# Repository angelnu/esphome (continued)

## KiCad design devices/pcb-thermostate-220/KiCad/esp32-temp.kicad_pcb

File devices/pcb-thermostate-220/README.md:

# Thermostate for 220v
This PCB allows controlling two relays based on 1 wire Dallas temperature sensors. The board has two 1-wire buses - one for the in-board sensor and one for the external sensor(s).
- 

- [Aisler PCB project](https://aisler.net/p/ORVQXQHK)
- [KiCad schematics](KiCad/esp32-temp.sch)
  - 
- [KiCad PCB](KiCad/esp32-temp.kicad_pcb)
  - 
  - 
  - 

- Parts:
  - 1x [ESP32-WROOM-32](https://www.espressif.com/sites/default/files/documentation/esp32-wroom-32_datasheet_en.pdf)
  - nx [Temperature Sensors - DS18B20](http://datasheets.maximintegrated.com/en/ds/DS18B20.pdf)
    - the sensor in the PCB is in format TO-92. I bought mine in ebay.
    - the external sensors are attached to the connector top lef. You can get them waterprof at many places including [Amazon](https://www.amazon.de/AZDelivery-digitaler-Temperatursensor-Temperaturf%C3%BChler-wasserdicht/dp/B075FV3PQR/ref=sr_1_8?dchild=1&keywords=DS18B20&qid=1598127886&sr=8-8)
  - 2x [5v 10A Relay](http://www.sanyourelay.ca/public/products/pdf/SRD.pdf)
  - 1x [220v-5V ACDC transformer](http://www.hlktech.net/product_detail.php?ProId=59)
  - 1x [xc6206 - 3,3v 0,5A regulator in SOT-23 format](https://www.torexsemi.com/file/xc6206/XC6206.pdf)
  - 2x [IRLML2060 - N-MOSFET](https://www.infineon.com/dgdl/irlml2060pbf.pdf?fileId=5546d462533600a401535664b7fb25ee)
- PINs:
  - Header top left - external temperature sensors. From top to bottom:
    - VCC
    - Data
    - GND
  - Header right - 220v input/oputput. From top to bottom:
    - Input - common
    - Input - phase
    - Relay 1 Output - Normally Closed -> connect here if device is usually powered
    - Relay 1 Output - common
    - Relay 1 Output - Nomally Open -> connect here if device is usually turned off
    - Relay 2 Output - Normally Closed -> connect here if device is usually powered
    - Relay 2 Output - common
    - Relay 2 Output - Nomally Open -> connect here if device is usually turned off
  - Header top - all unussed ESP32 GPIOs - usefull when other external sensors or outputs are needed
- Firmware: [esphome](esphome.io)
  - You need to modify/create your own esphome definition and include the yaml in this folder matching your PCB
  - [Example for v1.1](../../thermostate1_buhardilla.yaml)
- [3D Printed cage](cage):
  - 
  - 
  - 

# Changelog

## v1.2
  - Address bugs from first version PCB
    - moved internal temp sensor to GPIO15
    - connected relay MOSFETs to GPIO33 (Relay 1) and GPIO32 (Relay 2)
  - Same stencil as for v1.1
## v1.1
  - First version
  - BUGS:
    - MOSFET not connected to ESP32
      - solved with wire
    - 1-wire pull-up for internal temperature sensor prevents programming
      - solved by removing pull-up
      - internal sensor still working without pull-up

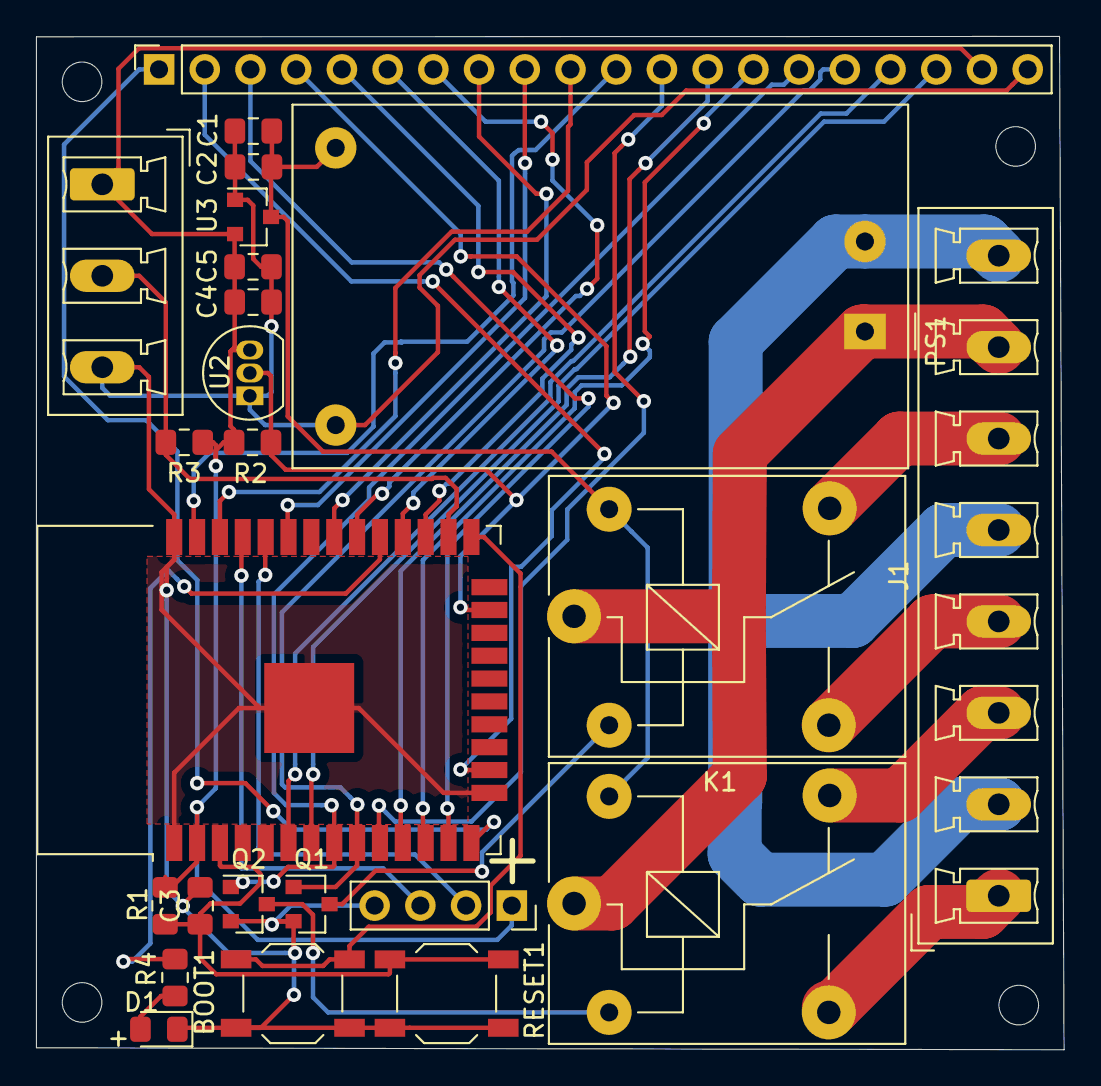
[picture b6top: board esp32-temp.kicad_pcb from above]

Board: 2 copper layers, 57.1 x 56.3 mm, 28 parts (0 on the bottom side), 36 nets.

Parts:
BOOT1: SW_Push; SW_SPST_TL3342
C1, C3, C4: 10uF; C_0805_2012Metric_Pad1.15x1.40mm_HandSolder
C2, C5: 100nF; C_0805_2012Metric_Pad1.15x1.40mm_HandSolder
D1: LED; D_0805_2012Metric_Pad1.15x1.40mm_HandSolder
H1, H2, H3, H4: MountingHole; MountingHole_2.2mm_M2
J1: 220V; PhoenixContact_MCV_1,5_8-G-5.08_1x08_P5.08mm_Vertical
J3: PROGRAM; PinSocket_1x04_P2.54mm_Vertical
J4: TEMP; PhoenixContact_MCV_1,5_3-G-5.08_1x03_P5.08mm_Vertical
J5: Conn_01x24_Male; PinSocket_1x20_P2.54mm_Vertical
K1, K2: SANYOU_SRD_Form_A; Relay_SPDT_SANYOU_SRD_Series_Form_C
PS1: HLK-PM05; Converter_ACDC_HiLink_HLK-PMxx
Q1, Q2: IRLML2060; SOT-23
R1, R4: 12K; R_0805_2012Metric_Pad1.15x1.40mm_HandSolder
R2, R3: 4K7; R_0805_2012Metric_Pad1.15x1.40mm_HandSolder
RESET1: SW_Push; SW_SPST_TL3342
U1: ESP32-WROOM-32
U2: DS18B20; TO-92_Inline
U3: XC6206PxxxMR; SOT-23

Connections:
+3V3: C4.1, C5.1, J3.1, J4.1, J5.19, R1.1, R2.1, R3.1, U1.2, U2.3, U3.2
+5V: C1.1, C2.1, K1.5, K2.5, PS1.4, U3.3
AC_N: J1.2, J1.5, J1.8, PS1.2
AC_P: J1.7, K1.1, K2.1, PS1.1
GND: BOOT1.2, C1.2, C2.2, C3.2, C4.2, C5.2, D1.1, J3.4, J4.3, J5.20, PS1.3, Q1.2, Q2.2, RESET1.1, U1.1, U1.15, U1.38, U1.39, U2.1, U3.1
unnamed: BOOT1.1, U1.25
unnamed: C3.1, R1.2, RESET1.2, U1.3
unnamed: D1.2, R4.2
unnamed: J1.1, K2.3
unnamed: J1.3, K2.4
unnamed: J1.4, K1.3
unnamed: J1.6, K1.4
unnamed: J3.2, U1.34
unnamed: J3.3, U1.35
unnamed: J4.2, R3.2, U1.26
unnamed: J5.1, U1.14
unnamed: J5.2, U1.16
unnamed: J5.3, U1.13
unnamed: J5.4, R2.2, U1.23, U2.2
unnamed: J5.5, U1.27
unnamed: J5.6, U1.28
unnamed: J5.7, U1.30
unnamed: J5.8, U1.31
unnamed: J5.9, U1.33
unnamed: J5.10, U1.36
unnamed: J5.11, U1.37
unnamed: J5.12, U1.10
unnamed: J5.13, U1.11
unnamed: J5.14, U1.12
unnamed: J5.17, U1.6
unnamed: J5.18, U1.7
unnamed: K1.2, Q1.3
unnamed: K2.2, Q2.3
unnamed: R4.1, U1.29
RELAY1: J5.16, Q1.1, U1.9
RELAY2: J5.15, Q2.1, U1.8

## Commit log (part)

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2019-12-24 First release
2020-04-10 Add all home devices
2020-04-10 moved
2020-04-13 fix uptime sensor name
2020-04-13 Add new devices
2020-04-13 Add some commented out options to tune
2020-04-14 Move uptime sensor to template
2020-04-14 Add new simple switches
2020-04-14 New power devices
2020-08-21 Classify devices
2020-08-22 Upload Thermostate readme
2020-08-22 Add schematics and instructions for interphone
2020-08-22 create folders for devices
2020-08-22 Add revision
2020-08-22 Fix foto
2020-08-22 Fix picture
2020-08-25 use default versions
2020-08-25 change IPs
2020-08-28 add pcb img
2020-08-28 Change sensor address
2020-08-29 First draft
2020-08-29 initial readme
2020-08-30 Added pictures to Temp Actor
2020-08-30 add one message to skipped trx in release mode
2020-08-31 Update of Pot watering Sensor
    Added pictures and cage
2020-09-19 add controller details
2020-09-20 Use package feature
2020-09-20 less verbose
2020-09-21 Add IC controller
2020-09-21 use namespace
2020-09-21 all sensors actor working
2020-10-10 template_lights
2020-10-10 rename to led
2020-10-11 use blue for cold white
2020-10-12 add flur leds wifi
2020-10-24 common light effects
2020-10-24 Add lights to guestroom
2020-10-25 Abstract remote
2021-01-13 Upload new lights
2021-01-13 test
2021-04-07 test_neo
2021-04-11 led bedroom bed
2021-09-11 add leds
2021-09-12 rename d2
2021-09-12 change IP
2021-09-12 bedroom bed led
2021-10-19 add support to togle on reset
2021-10-19 use l17
2021-11-01 rename devices
2022-01-08 Add trashcan
2022-01-08 remove old prototypr
2022-01-08 add more lights
2022-01-09 documented tashcan
2022-01-09 power usb defines
2022-01-10 update to kicad 6
2022-01-10 PCB for USB
2022-01-11 add readme, cage and firmware
2022-01-11 add some recovery code
2022-01-16 update ignore file
2022-01-17 refreshed step model
2022-01-18 complete readme with pictures
2022-01-18 update to use first filament
2022-01-18 remove holgura from lid
2022-01-18 place lid on external face
2022-10-16 add default renovate
2022-11-05 update bot email
2023-01-02 add readme
2023-01-02 support for static ips
2023-01-02 add missing $
2023-01-02 document wifi roaming feaure
2023-01-02 fix ips
2023-01-02 commit new devices
2023-06-22 add 3d printed parts
2023-06-22 Exported Fusion360 model
2023-09-13 initial release
2023-09-27 split ade7953 sensor
2023-09-27 added compatibility layer
2023-09-27 add support for display and power sensors
2023-09-29 update Shelly Pro 4PM devices
2023-09-29 add API restart timeout
2023-09-29 add ADE7953 rework
2023-10-07 adjust gains
2024-08-20 sync changes
2024-09-01 use new web server for esp32
2024-09-01 merged change
2024-09-01 solar splitter
2024-09-01 leds pueblo
2024-09-01 add box and freecad files
2024-09-01 add box
2024-09-01 add gitignore
2024-09-09 link cad files
2024-09-09 add resistances
2024-09-09 remove tmp file
2024-09-13 add pictures
2024-09-13 remove dup link
2025-07-13 move unused
2025-07-13 rework
2025-07-17 add pcb
2025-07-17 ignore mac indexes
2025-07-19 update interphone
2025-07-20 progress with siedle
2025-07-21 working siedle send
2025-07-26 first working version working
2025-07-27 split command in parts
2025-07-27 adjust log level
2025-07-27 rename to Message
2025-07-27 split message header into cpp
2025-07-27 clean readme
2025-07-27 add cage
2025-07-27 make box thicker
2025-07-27 remove unused components
2025-07-27 wait for receive to finish
2025-07-27 upload picture
2025-07-27 prepare for improved interrupts
2025-07-28 collect msgs
2025-07-28 log unexpected msg parts
2025-07-28 reduce slack
2025-07-28 export cage
2025-07-28 group
2025-07-28 describe FreeCAD parameters
2025-07-28 change alignments
2025-07-28 fix alignment
2025-07-28 improve README firmware
2025-08-01 fix typo
2025-08-01 use variables
2025-08-02 add larger cage
2025-08-02 add more holes
2025-08-02 rename
2025-08-02 fix holes
2025-08-02 refresh
2025-08-02 add placement template
2025-08-02 update schematics
2025-08-02 wait longer after receiving
2025-08-02 update pictures
2025-08-03 increase frequency
2025-08-03 log unexpected msg
2025-08-03 wait longer after transferring
2025-08-03 send initial binary sensor state
2025-08-04 use esp-idf
2025-08-04 move to esp-idf
2025-08-20 pcb-leds with esp32
2025-08-20 improve led rf
2025-08-20 use esp32-c6
2025-08-20 readme for Led PCB
2025-08-20 fix links
2025-08-29 document parts
2025-08-29 add assembly
2025-09-08 working new PCB leds
2025-09-08 update box
2025-09-17 pcb lights
2025-09-17 compat
2025-09-17 activate device
2025-09-17 updated to esp32
2025-09-17 compat network
2025-09-17 add new secrets
2025-09-27 add ikea closets
2025-10-04 upgrade workroom
2025-10-05 upgrade devices
2025-10-10 Update README.md
    Updating parts list to include alternate sources for some parts, a source for the ESP32 & D1+D2 which were missing entirely.
2025-10-25 replace lights livingroom
2025-10-25 do not use bluetooth
2025-10-26 replace with esp32
2025-10-26 cover alicia
2025-10-26 specify framework
2025-10-26 add diode
2025-10-26 more info on cmds
2025-10-26 add build flags
2025-10-26 esp8266 does not support framework
2025-11-09 adapt box to larger PCB
2025-11-09 inprove readme
2025-11-09 add detail on LED
2025-11-09 unused strip led PCBs
2025-11-09 more info
2025-11-09 fix reference to ledc
2025-11-09 add tradfri link
2025-11-24 replace devices
2026-03-15 working pro4pm with esp-idf
2026-03-29 works on esphome 2026.3.1
2026-03-29 fix for new esphome
2026-03-29 update display and accumulate energy
2026-03-29 check before reading state
2026-03-29 remove firetv switch
2026-03-29 remove old switches
2026-05-14 add delay for wifi start
2026-06-20 Edit c06-bedroom.yaml
2026-06-20 Edit c04-dani-right.yaml
2026-06-20 Edit c08-workroom.yaml
2026-06-20 Edit c02-livingroom.yaml
2026-06-20 Edit c07-alicia.yaml
2026-06-20 Edit c05-guestroom.yaml
